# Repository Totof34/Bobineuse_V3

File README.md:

Bobineuse_V3
============

The project describes a stand-alone coil winder

If you would have more information about this project please visit 
www.audiyofan.org

A link to the dedicated post 
http://www.audiyofan.org/forum/viewtopic.php?f=73&t=7176&start=105

PCB & schema are designed with Kicad

the motor part uses a DC motor with a home made supply described below

The prototype of the display and the buttons

The optical fork's disc 

Everything that goes around the Leonardo's board

Here the function than my program include and which seems to me appropriate

 1° automatic counting and uncounting
 
 2° counting from zero or down from a specified number of turns
 
 3° initial point or initial carcass start recordable and reminder 
 
 4° guide wire enslaved on the up / down counting
 
 5° automatic reversing guide wire depending on the number of turns per layer and change side
 
 6° manual correction of errors in advance of the guide wire, losses step essentially
 
 7° Manual correction of counting errors
 
 8° management parameters by a "management" menu and a second separate part for the counting itself
 
 9° recordings of 10 different configurations to facilitate the winding of several transformers,
    by recording the primary and secondary sections separately and recall stored data in memory
    
10° display menus on 16x2 characters LCD

Of course my Leonardo's board also allows PC control if you wanted to, but I prefer a
standalone machine

See in the arduino folder for the sketch

Detail of the guidewire

Implementation of electronic boards in progress

Work in progress

The coilwinder in function 

Addition of a carrier for high copper coil

All comments are welcome

Totof

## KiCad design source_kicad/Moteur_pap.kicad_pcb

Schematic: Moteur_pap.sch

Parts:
C1: 220µ
C2, C4: 10µ
C3: 100n
C5: 100µ
D1: ZENER24V
K1: POT_VIT
K2: ILS1
K3: ILS2
P1: CONN_B+
P2: IN1_2
P3: IN3_4
P4: WIPPER
P5, P19, P21, P22: +5V
P6: MOT1
P7: MOT2
P8: ALIM_MOT
P9: ILS1
P10, P12: PB1
P11, P13: PB3
P14, P17: PB2
P15, P18: PB4
P16: ILS2
P20: LVO
P23, P24: TST
R1: 220
R2, R3, R4, R5, R6, R7, R8: 10K
RV1: POT10K
U1: LM7805CT; TO-220
U2: ULN2003

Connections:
+5V: C3.1, C4.1, K1.1, K2.1, K3.1, P5.1, P12.1, P13.1, P17.1, P18.1, P19.1, P21.1, P22.1, RV1.1, U1.3 (OUT); also elsewhere on the board
+12V: C1.1, D1.1, P1.1, P8.1, P8.2 (PM), R1.1, R2.1
GND: C1.2, C2.2, C3.2, C4.2, C5.2, K1.3, P1.2 (PM), P5.2 (PM), P19.2 (PM), P21.2 (PM), P22.2 (PM), R3.2, R4.2, R5.2, R6.2, R7.2, R8.2, RV1.3, U1.2 (GND), U2.5 (I5), U2.6 (I6), U2.7 (I7), U2.8 (GND); also elsewhere on the board
unnamed: C2.1, R1.2, U1.1 (IN)
unnamed: C5.1, R2.2
unnamed: D1.2, U2.9 (COM)
unnamed: K1.2 (PM), P4.1
unnamed: K2.2 (PM), P9.1, P9.2 (PM)
unnamed: K2.3, R3.1
unnamed: K3.2 (PM), P16.1, P16.2 (PM)
unnamed: K3.3, R6.1
unnamed: P2.1, U2.1 (I1)
unnamed: P2.2 (PM), U2.2 (I2)
unnamed: P3.1, U2.3 (I3)
unnamed: P3.2 (PM), U2.4 (I4)
unnamed: P6.1, U2.16 (O1)
unnamed: P6.2 (PM), U2.15 (O2)
unnamed: P7.1, U2.14 (O3)
unnamed: P7.2 (PM), U2.13 (O4)
unnamed: P10.1, P12.2 (PM), R4.1
unnamed: P11.1, P13.2 (PM), R5.1
unnamed: P14.1, P17.2 (PM), R7.1
unnamed: P15.1, P18.2 (PM), R8.1
unnamed: P20.1, RV1.2

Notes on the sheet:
Copyleft 2014 Christophe Dedessus Les Moutier License CC by SA htpp://www.audiyofan.org

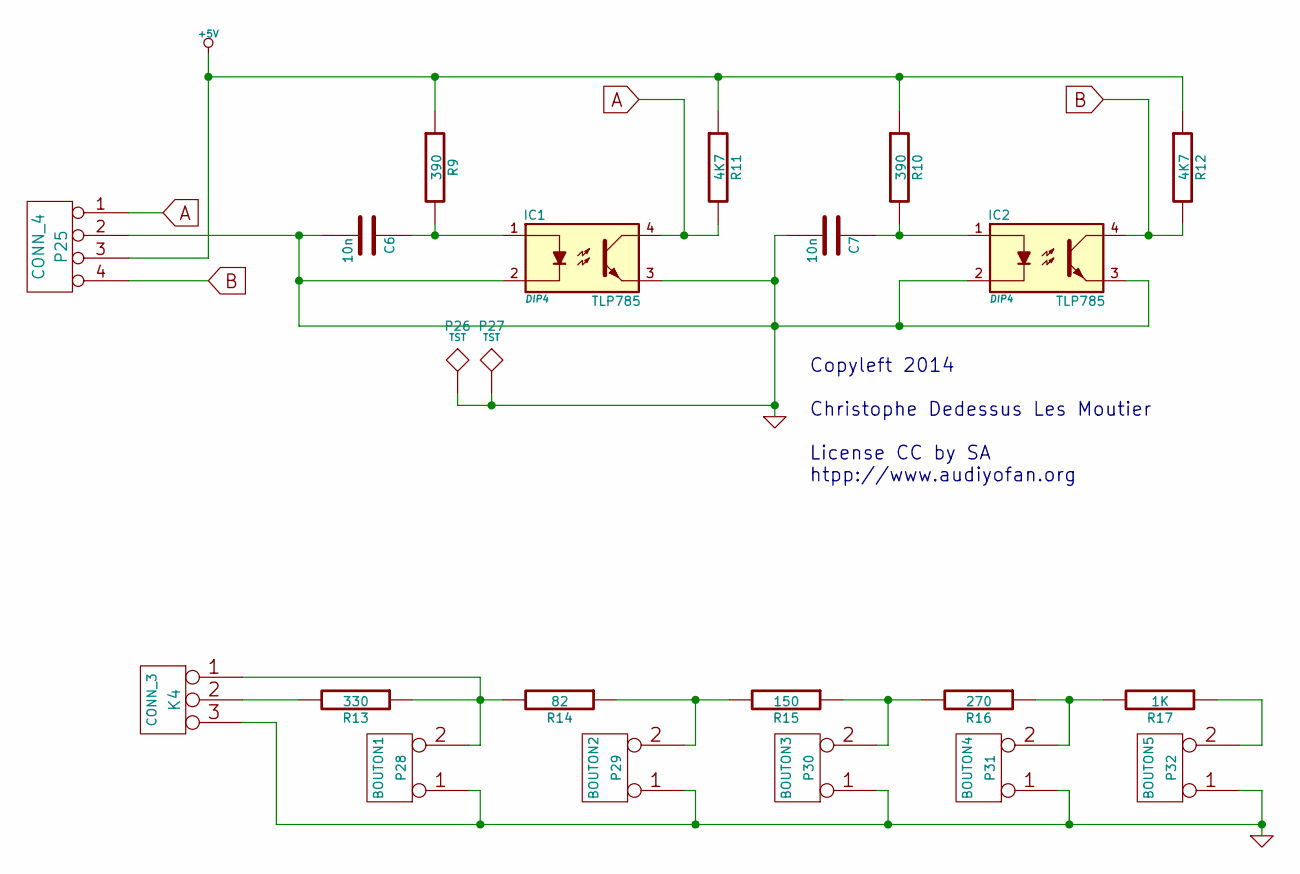
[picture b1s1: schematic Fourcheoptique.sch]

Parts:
C6, C7: 10n
IC1, IC2: TLP785; DIP4
K4: CONN_3
P25: CONN_4
P26, P27: TST
P28: BOUTON1
P29: BOUTON2
P30: BOUTON3
P31: BOUTON4
P32: BOUTON5
R9, R10: 390
R11, R12: 4K7
R13: 330
R14: 82
R15: 150
R16: 270
R17: 1K

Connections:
+5V: P25.3, R9.1, R10.1, R11.1, R12.1; also elsewhere on the board
A: IC1.4, P25.1, R11.2
B: IC2.4, P25.4, R12.2
GND: C6.2, C7.2, IC1.2, IC1.3, IC2.2, IC2.3, K4.3, P25.2, P26.1, P27.1, P28.1, P29.1, P30.1, P31.1, P32.1; also elsewhere on the board
unnamed: C6.1, IC1.1, R9.2
unnamed: C7.1, IC2.1, R10.2
unnamed: K4.1, P28.2 (PM), R13.1, R14.2
unnamed: K4.2 (PM), R13.2
unnamed: P29.2 (PM), R14.1, R15.2
unnamed: P30.2 (PM), R15.1, R16.2
unnamed: P31.2 (PM), R16.1, R17.2
unnamed: P32.2 (PM), R17.1

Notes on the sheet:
Copyleft 2014 Christophe Dedessus Les Moutier License CC by SA htpp://www.audiyofan.org

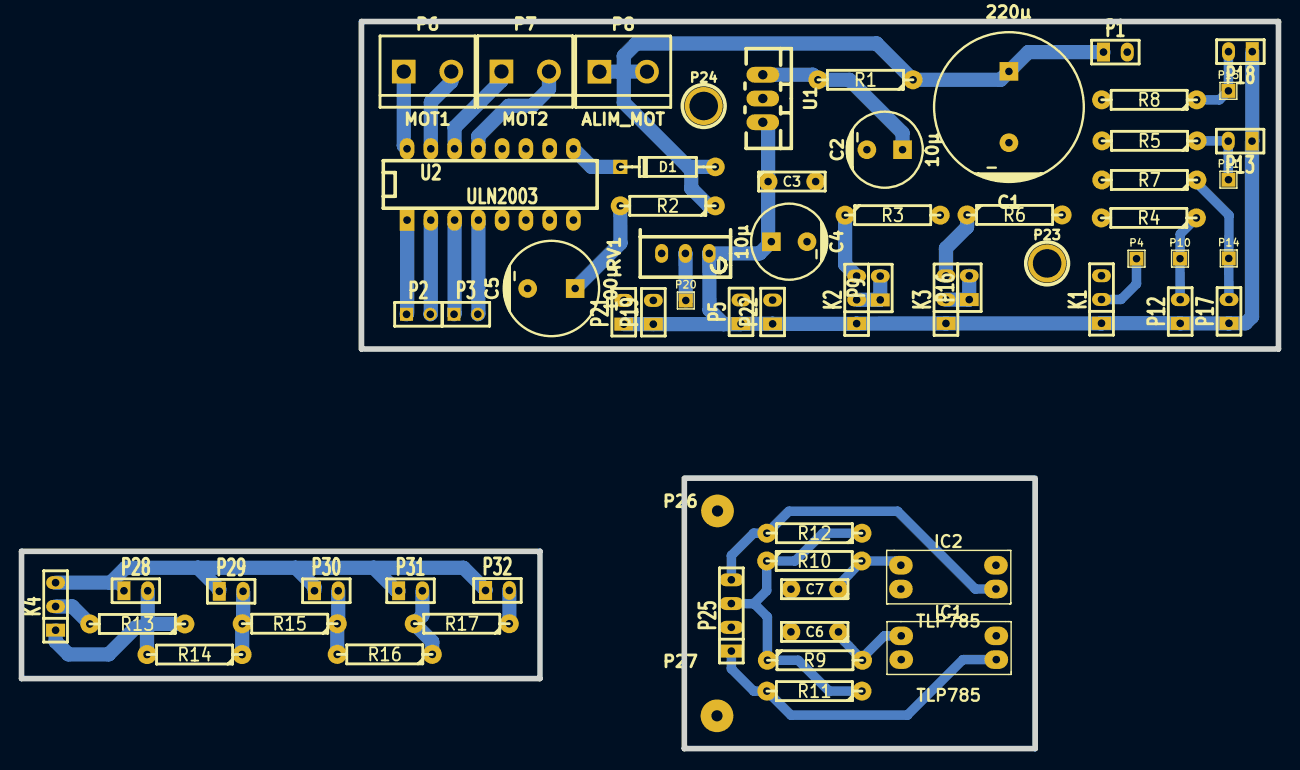
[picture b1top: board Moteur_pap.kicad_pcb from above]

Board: 2 copper layers, 134.3 x 77.7 mm, 66 parts (0 on the bottom side), 34 nets.

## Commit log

2014-04-13 First commit Somme files are added, schématics, pictures, kicad's source files
2014-04-13 Add a picture of the coil winder in README.md
2014-04-13 Schema with the Leonardo board added
2014-04-14 Add a picture of the display and the buttons
2014-04-14 Update the readme file
2014-04-27 Little bug corrected in counter display with negative value
2014-04-27 Front design added with source file in fpl format
2014-04-27 Add a new picture of the work in progress
2014-04-29 Display modified and managing a first point for easy reset
2014-05-01 Added program explanation
2014-05-01 New picture of the guidewire & Fixed a display bug when resetting counter
2014-05-02 Picture of the steppermotror added
2014-05-02 add picture's electronic board
2014-05-03 adding images reconstruction
2014-05-03 Update the README with the work in progress
2014-05-03 add 2 picture of the guidewire
2014-05-05 Add 2 new pictures of the wire reel
2014-05-06 Add the optical fork's disc & source file
2014-05-07 Add new picture of the guidewire & the brake system
2014-05-11 Add picture of the coilwinder in function
2014-05-19 Addition of a carrier for high copper coil
